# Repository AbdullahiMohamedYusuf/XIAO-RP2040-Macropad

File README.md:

XIAO RP2040 Macropad

A compact 9-key macropad with a rotary encoder, built around the Seeed Studio XIAO RP2040 and running CircuitPython. 
It comes with a custom PCB designed in KiCad and a snap-fit 3D-printed case that needs no screws.

Features
3×3 grid of MX-style mechanical switches
EC11 rotary encoder with push button
Seeed XIAO RP2040 with USB-C
Programmed in CircuitPython: just edit code.py, no compiling
Snap-fit case and knob, printable without screws

Bill of materials
1x	Seeed Studio XIAO RP2040
9x	MX-style mechanical switches
9x	SOD-123 diodes
1x	EC11 rotary encoder (D-shaft)
9x	MX-compatible keycaps
1x	3D-printed case (tray + lid) and knob

Ordering the PCB

Upload the Gerber files from pcb/production/ to a PCB manufacturer such as JLCPCB or PCBWay. 
The default options (2 layers, 1.6 mm thickness) work fine.

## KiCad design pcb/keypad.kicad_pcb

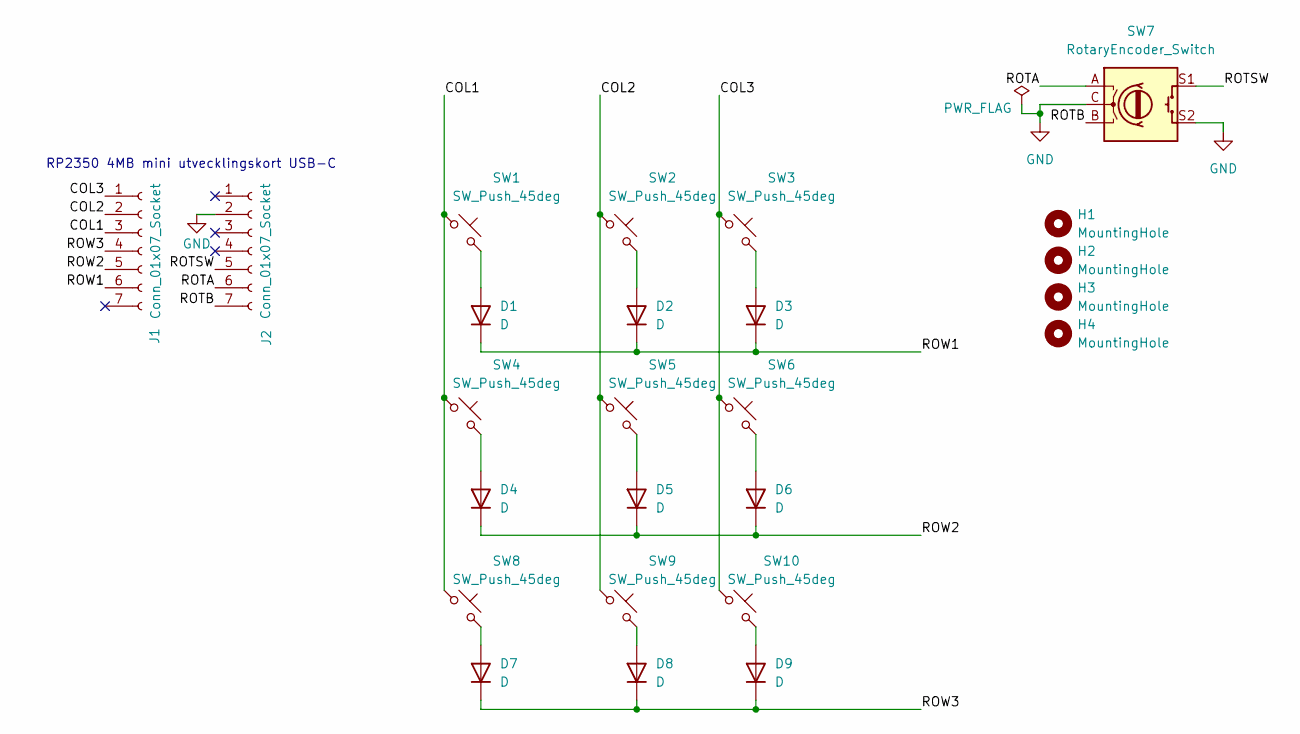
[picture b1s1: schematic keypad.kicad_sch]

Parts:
D1, D2, D3, D4, D5, D6, D7, D8, D9: D; D_SOD-123
H1, H2, H3, H4: MountingHole; MountingHole_2.2mm_M2
J1, J2: Conn_01x07_Socket; PinSocket_1x07_P2.54mm_Vertical
SW1, SW2, SW3, SW4, SW5, SW6, SW8, SW9, SW10: SW_Push_45deg; SW_Cherry_MX_1.00u_PCB
SW7: RotaryEncoder_Switch; RotaryEncoder_Alps_EC11E-Switch_Vertical_H20mm

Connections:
/COL1: J1.3, SW1.1, SW4.1, SW8.1
/COL2: J1.2, SW2.1, SW5.1, SW9.1
/COL3: J1.1, SW3.1, SW6.1, SW10.1
/ROTA: J2.6, SW7.A
/ROTB: J2.7, SW7.B
/ROTSW: J2.5, SW7.S1
/ROW1: D1.1 (K), D2.1 (K), D3.1 (K), J1.6
/ROW2: D4.1 (K), D5.1 (K), D6.1 (K), J1.5
/ROW3: D7.1 (K), D8.1 (K), D9.1 (K), J1.4
GND: J2.2, SW7.C, SW7.S2
unnamed: D1.2 (A), SW1.2
unnamed: D2.2 (A), SW2.2
unnamed: D3.2 (A), SW3.2
unnamed: D4.2 (A), SW4.2
unnamed: D5.2 (A), SW5.2
unnamed: D6.2 (A), SW6.2
unnamed: D7.2 (A), SW8.2
unnamed: D8.2 (A), SW9.2
unnamed: D9.2 (A), SW10.2

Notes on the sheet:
RP2350 4MB mini utvecklingskort USB-C

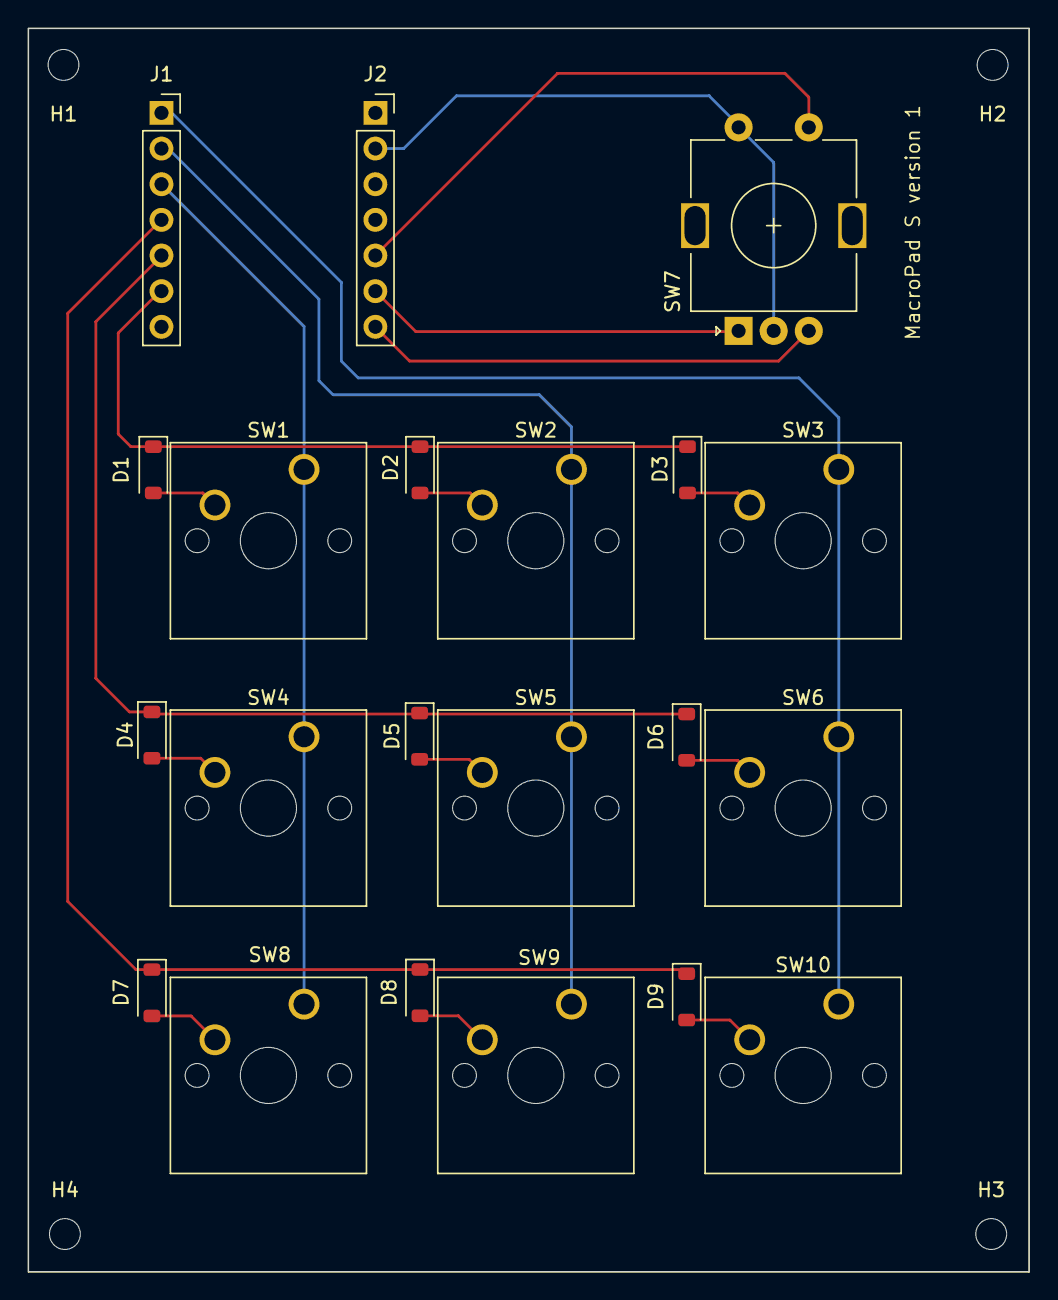
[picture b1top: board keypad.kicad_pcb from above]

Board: 2 copper layers, 71.3 x 88.6 mm, 25 parts (0 on the bottom side), 19 nets.

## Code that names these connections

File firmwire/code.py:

import time
import microcontroller
import digitalio
import keypad
import rotaryio
import usb_hid
from adafruit_hid.keyboard import Keyboard
from adafruit_hid.keycode import Keycode
from adafruit_hid.consumer_control import ConsumerControl
from adafruit_hid.consumer_control_code import ConsumerControlCode

# Initialize USB Devices
keyboard = Keyboard(usb_hid.devices)
cc = ConsumerControl(usb_hid.devices)

# --- Fixed Pin Mapping ---
row_pins = (
    microcontroller.pin.GPIO7,   # ROW1 (D5) - Top
    microcontroller.pin.GPIO6,   # ROW2 (D4) - Middle
    microcontroller.pin.GPIO29,  # ROW3 (D3) - Bottom
)

col_pins = (
    microcontroller.pin.GPIO28,  # COL1 (D2) - Left
    microcontroller.pin.GPIO27,  # COL2 (D1) - Middle
    microcontroller.pin.GPIO26,  # COL3 (D0) - Right
)

# Rotary Encoder Setup
encoder = rotaryio.IncrementalEncoder(microcontroller.pin.GPIO2, microcontroller.pin.GPIO1)  # ROTA = D8, ROTB = D7

rot_sw = digitalio.DigitalInOut(microcontroller.pin.GPIO4)  # ROTSW = D9
rot_sw.direction = digitalio.Direction.INPUT
rot_sw.pull = digitalio.Pull.UP

matrix = keypad.KeyMatrix(row_pins, col_pins)

# --- Mode Configurations ---
MODE_NAMES = ["YouTube", "KiCad Schematic"]
current_mode = 0

keymaps = [
    # Mode 0: YouTube
    [
        Keycode.J,            Keycode.K,            Keycode.L,             # Top Left | Top Mid | Top Right
        Keycode.M,            Keycode.F,            Keycode.C,             # Mid Left | Mid Mid | Mid Right
        Keycode.LEFT_ARROW,   Keycode.SPACE,        Keycode.RIGHT_ARROW    # Bot Left | Bot Mid | Bot Right
    ],
    # Mode 1: KiCad Schematic
    [
        Keycode.A,            Keycode.W,            Keycode.L,             # Top Left (A) | Top Mid (W) | Top Right (L)
        Keycode.P,            Keycode.Q,            Keycode.R,             # Mid Left (P) | Mid Mid (Q) | Mid Right (R)
        Keycode.E,            Keycode.DELETE,       Keycode.ESCAPE  # Bot Left | Bot Mid | Bot Right
    ]
]

last_sw_state = True
last_encoder_pos = encoder.position

print(f"Macropad Ready! Active Mode: {MODE_NAMES[current_mode]}")

def trigger_key(key_def, is_pressed):
    if isinstance(key_def, tuple):
        if is_pressed:
            for k in key_def:
                keyboard.press(k)
        else:
            for k in reversed(key_def):
                keyboard.release(k)
    else:
        if is_pressed:
            keyboard.press(key_def)
        else:
            keyboard.release(key_def)

while True:
    # 1. Rotary Switch Press -> Change Mode
    current_sw_state = rot_sw.value
    if last_sw_state and not current_sw_state:
        current_mode = (current_mode + 1) % len(keymaps)
        print("Switched Mode ->", MODE_NAMES[current_mode])
        time.sleep(0.05)
    last_sw_state = current_sw_state

    # 2. Rotary Encoder Rotation -> Volume Control
    current_pos = encoder.position
    if current_pos != last_encoder_pos:
        diff = current_pos - last_encoder_pos
        last_encoder_pos = current_pos

        if diff > 0:
            for _ in range(abs(diff)):
                cc.send(ConsumerControlCode.VOLUME_INCREMENT)
        else:
            for _ in range(abs(diff)):
                cc.send(ConsumerControlCode.VOLUME_DECREMENT)

    # 3. Key Matrix Scanning
    matrix_event = matrix.events.get()
    if matrix_event:
        selected_key = keymaps[current_mode][matrix_event.key_number]
        trigger_key(selected_key, matrix_event.pressed)     
